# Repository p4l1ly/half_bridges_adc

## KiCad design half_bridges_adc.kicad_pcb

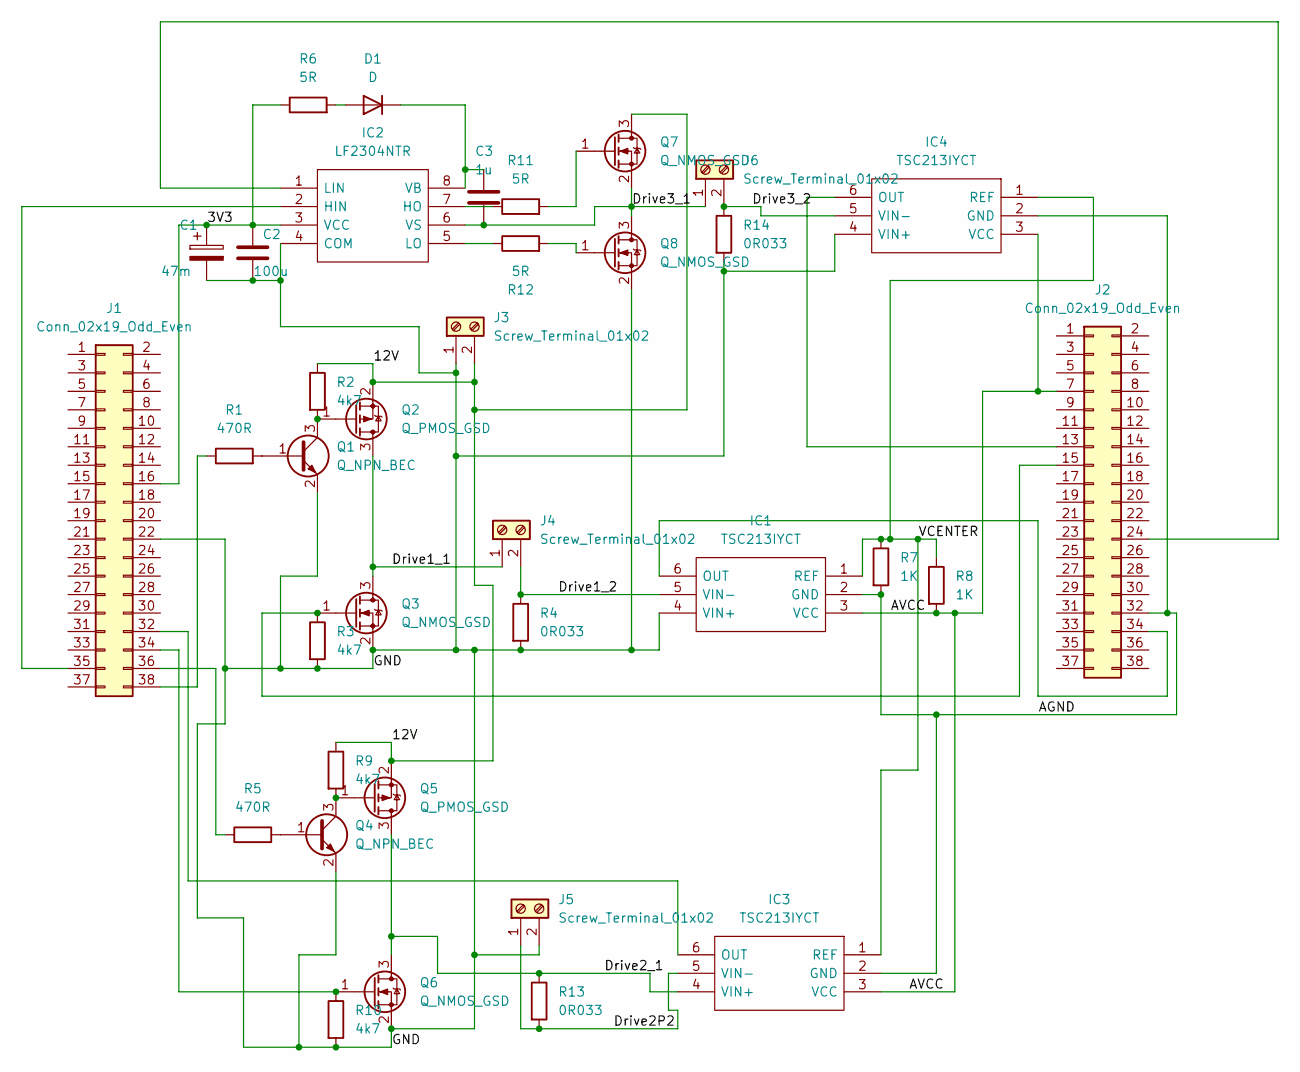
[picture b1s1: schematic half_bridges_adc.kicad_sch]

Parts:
C1: 47m; CP_Radial_D18.0mm_P7.50mm
C2: 100u; C_0805_2012Metric
C3: 1u; C_0805_2012Metric
D1: D; D_SOD-123
IC1, IC3, IC4: TSC213IYCT; SOT-363_SC-70-6_Handsoldering; Mouser Part Number 511-TSC213IYCT
IC2: LF2304NTR; SOIC127P600X175-8N; Mouser Part Number 747-LF2304NTR
J1, J2: Conn_02x19_Odd_Even; Samtec_HLE-119-02-xx-DV-PE-LC_2x19_P2.54mm_Horizontal
J3, J4, J5, J6: Screw_Terminal_01x02; TerminalBlock_Phoenix_MPT-0,5-2-2.54_1x02_P2.54mm_Horizontal
Q1, Q4: Q_NPN_BEC; SOT-23
Q2, Q5: Q_PMOS_GSD; SOT-23-3
Q3, Q6, Q7, Q8: Q_NMOS_GSD; SOT-23-3
R1, R5: 470R; R_0603_1608Metric_Pad0.98x0.95mm_HandSolder
R2, R3, R9, R10: 4k7; R_0603_1608Metric_Pad0.98x0.95mm_HandSolder
R4, R13, R14: 0R033; R_0805_2012Metric_Pad1.20x1.40mm_HandSolder
R6, R11, R12: 5R; R_0603_1608Metric_Pad0.98x0.95mm_HandSolder
R7, R8: 1K; R_0603_1608Metric_Pad0.98x0.95mm_HandSolder

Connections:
/3V3: C1.1, C2.1, IC2.3 (VCC), J1.16, R6.1
/12V: J3.2, Q2.2 (S), Q5.2 (S), Q7.3 (D), R2.1, R9.1
/AGND: IC1.2 (GND), IC3.2 (GND), IC4.2 (GND), J2.32, R7.2
/AVCC: IC1.3 (VCC), IC3.3 (VCC), IC4.3 (VCC), J2.7, R8.2
/Drive1_1: J4.1, Q2.3 (D), Q3.3 (D)
/Drive1_2: IC1.5 (VIN-), J4.2, R4.1
/Drive2P2: IC3.5 (VIN-), J5.1, R13.2
/Drive2_1: IC3.4 (VIN+), Q5.3 (D), Q6.3 (D), R13.1
/Drive3_1: C3.2, IC2.6 (VS), J6.1, Q7.2 (S), Q8.3 (D)
/Drive3_2: IC4.5 (VIN-), J6.2, R14.1
/GND: C1.2, C2.2, IC1.4 (VIN+), IC2.4 (COM), IC4.4 (VIN+), J1.22, J3.1, J5.2, Q1.2 (E), Q3.2 (S), Q4.2 (E), Q6.2 (S), Q8.2 (S), R3.2, R4.2, R10.2, R14.2
/VCENTER: IC1.1 (REF), IC3.1 (REF), IC4.1 (REF), R7.1, R8.1
unnamed: C3.1, D1.1 (K), IC2.8 (VB)
unnamed: D1.2 (A), R6.2
unnamed: IC1.6 (OUT), J2.34
unnamed: IC2.1 (LIN), J2.24
unnamed: IC2.5 (LO), R12.1
unnamed: IC2.7 (HO), R11.1
unnamed: IC4.6 (OUT), J2.13
unnamed: IC3.6 (OUT), J1.32
unnamed: J1.34, Q6.1 (G), R10.1
unnamed: IC2.2 (HIN), J1.35
unnamed: J1.36, R5.1
unnamed: J1.38, R1.1
unnamed: J2.15, Q3.1 (G), R3.1
unnamed: Q1.1 (B), R1.2
unnamed: Q1.3 (C), Q2.1 (G), R2.2
unnamed: Q4.1 (B), R5.2
unnamed: Q4.3 (C), Q5.1 (G), R9.2
unnamed: Q7.1 (G), R11.2
unnamed: Q8.1 (G), R12.2

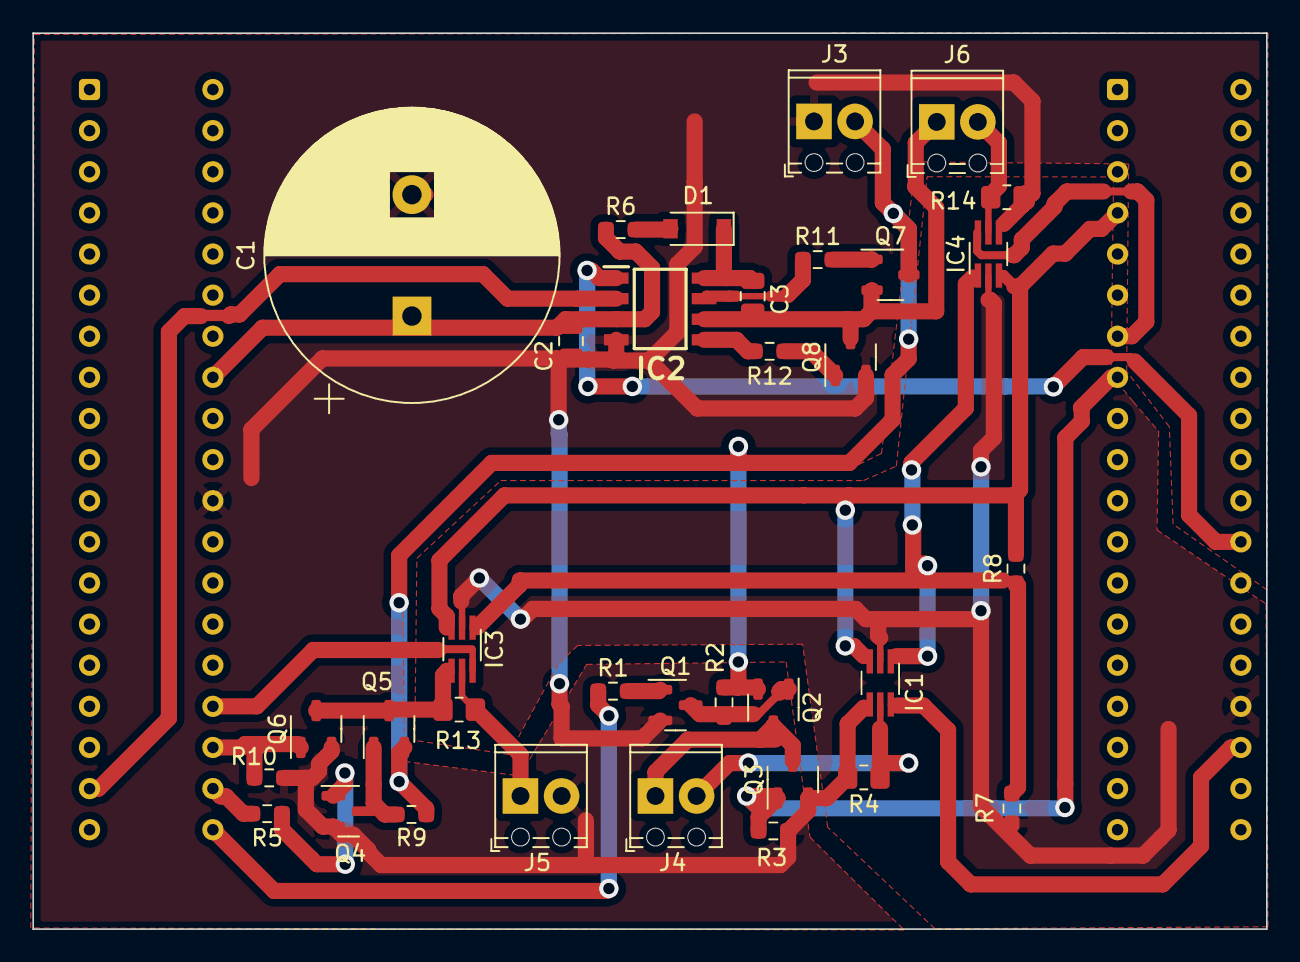
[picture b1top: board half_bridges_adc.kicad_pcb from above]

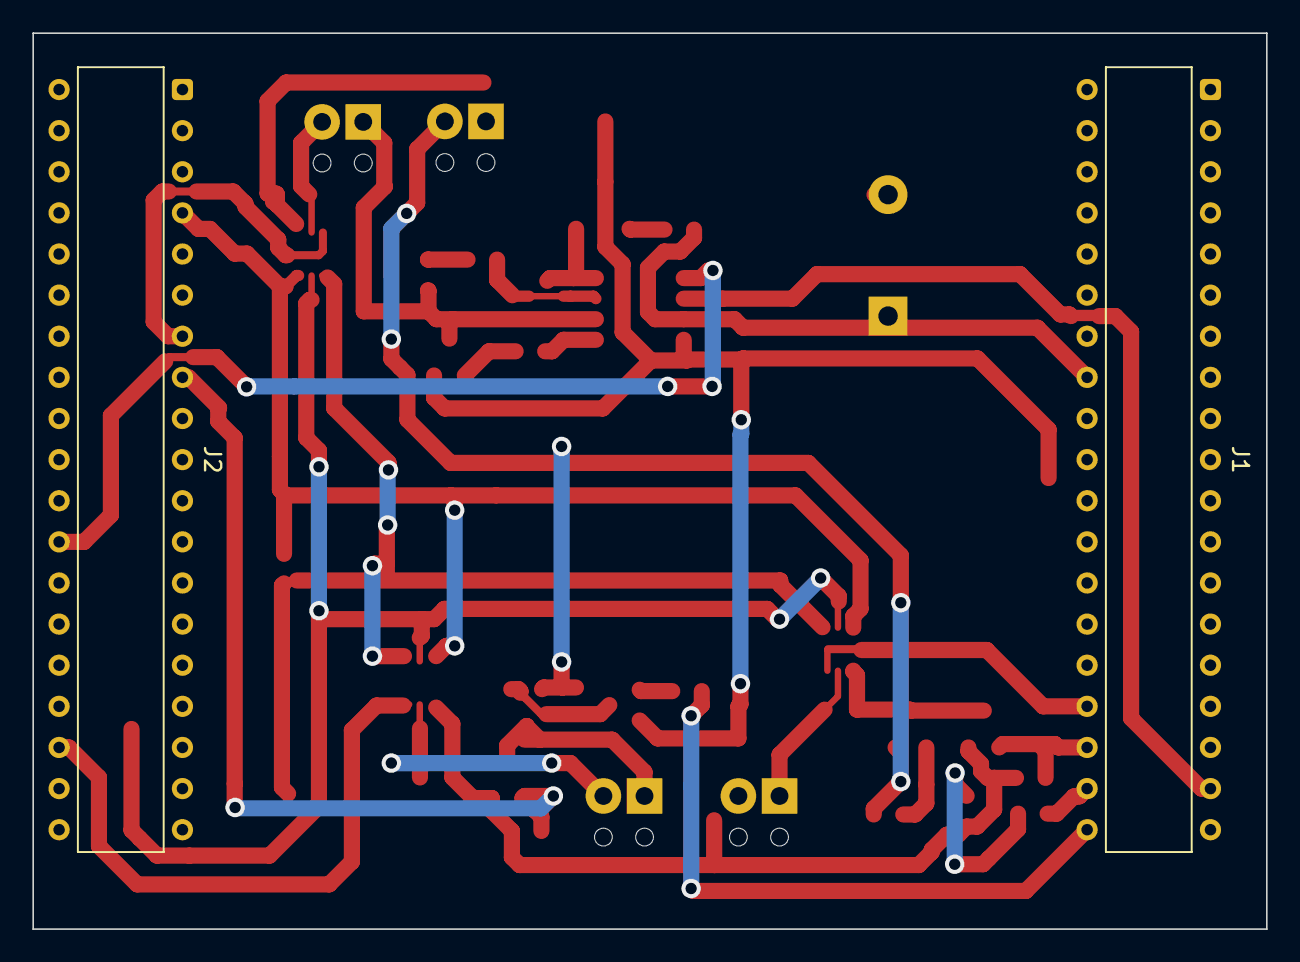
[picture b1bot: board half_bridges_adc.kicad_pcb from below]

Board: 2 copper layers, 76.2 x 55.3 mm, 36 parts (2 on the bottom side), 31 nets.

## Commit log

2023-03-04 minimum clearance 0 -> 0.25mm
2023-03-15 fix: move right connextor 2.54mm to the right
